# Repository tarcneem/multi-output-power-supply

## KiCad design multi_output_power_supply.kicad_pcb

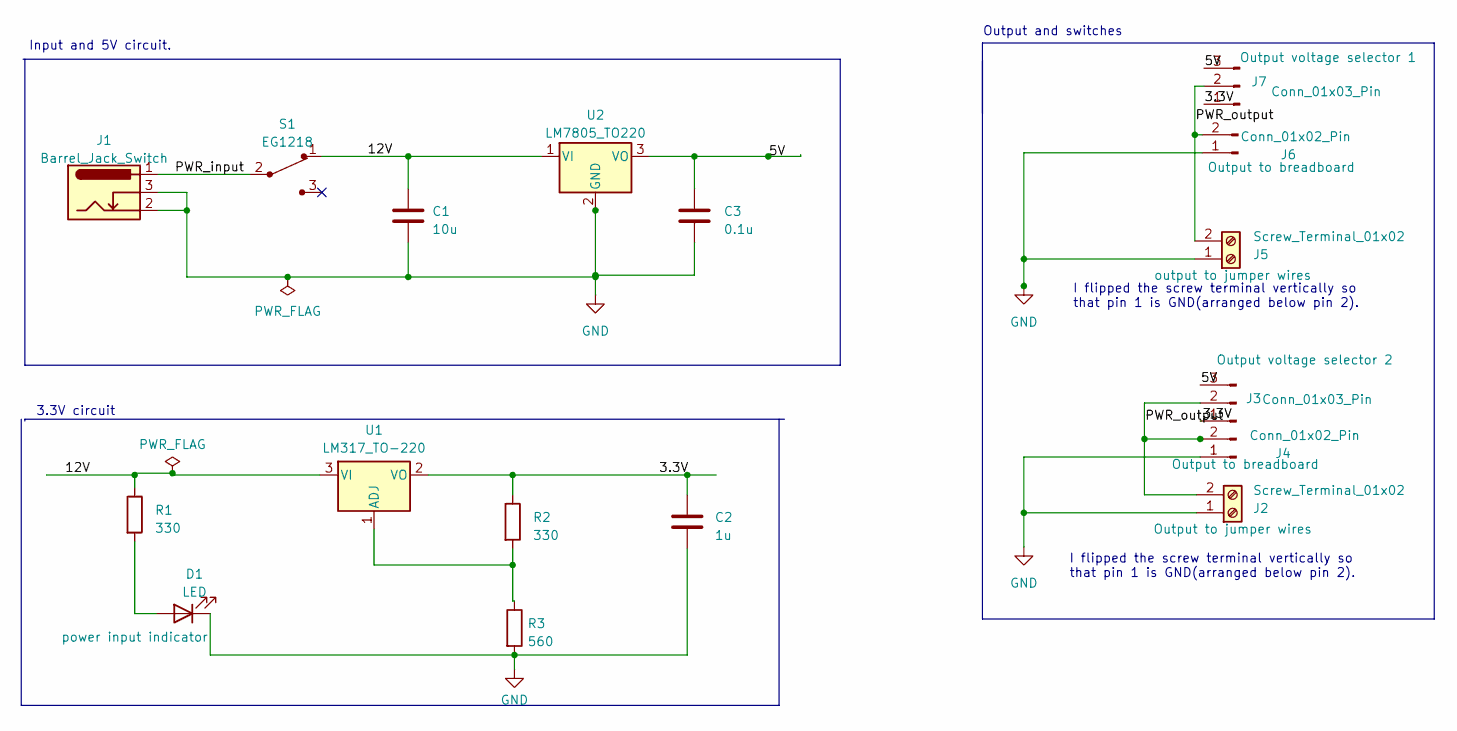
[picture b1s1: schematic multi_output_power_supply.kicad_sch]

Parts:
C1: 10u; C_Disc_D3.0mm_W1.6mm_P2.50mm
C2: 1u; C_Disc_D3.0mm_W1.6mm_P2.50mm
C3: 0.1u; C_Disc_D3.0mm_W1.6mm_P2.50mm
D1: LED; LED_D5.0mm
J1: Barrel_Jack_Switch; BarrelJack_Horizontal
J2, J5: Screw_Terminal_01x02; TerminalBlock_bornier-2_P5.08mm
J3, J7: Conn_01x03_Pin; PinHeader_1x03_P2.54mm_Vertical
J4, J6: Conn_01x02_Pin; PinHeader_1x02_P2.54mm_Vertical
R1, R2: 330; R_Axial_DIN0204_L3.6mm_D1.6mm_P7.62mm_Horizontal
R3: 560; R_Axial_DIN0204_L3.6mm_D1.6mm_P7.62mm_Horizontal
S1: EG1218; Switch_Slide_11.6x4mm_EG1218; MPN EG1218; Digi-Key_PN EG1903-ND
U1: LM317_TO-220; TO-220-3_Vertical
U2: LM7805_TO220; TO-220-3_Vertical

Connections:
/3.3V: C2.1, J3.1, J7.1, R2.1, U1.2 (VO)
/5V: C3.1, J3.3, J7.3, U2.3 (VO)
/12V: C1.1, R1.1, S1.1, U1.3 (VI), U2.1 (VI)
/PWR_input: J1.1, S1.2
/PWR_output: J2.2, J3.2, J4.2, J5.2, J6.2, J7.2
GND: C1.2, C2.2, C3.2, D1.1 (K), J1.2, J1.3, J2.1, J4.1, J5.1, J6.1, R3.2, U2.2 (GND)
unnamed: D1.2 (A), R1.2
unnamed: R2.2, R3.1, U1.1 (ADJ)

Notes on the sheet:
I flipped the screw terminal vertically so that pin 1 is GND(arranged below pin 2).
3.3V circuit
Output and switches
Input and 5V circuit.

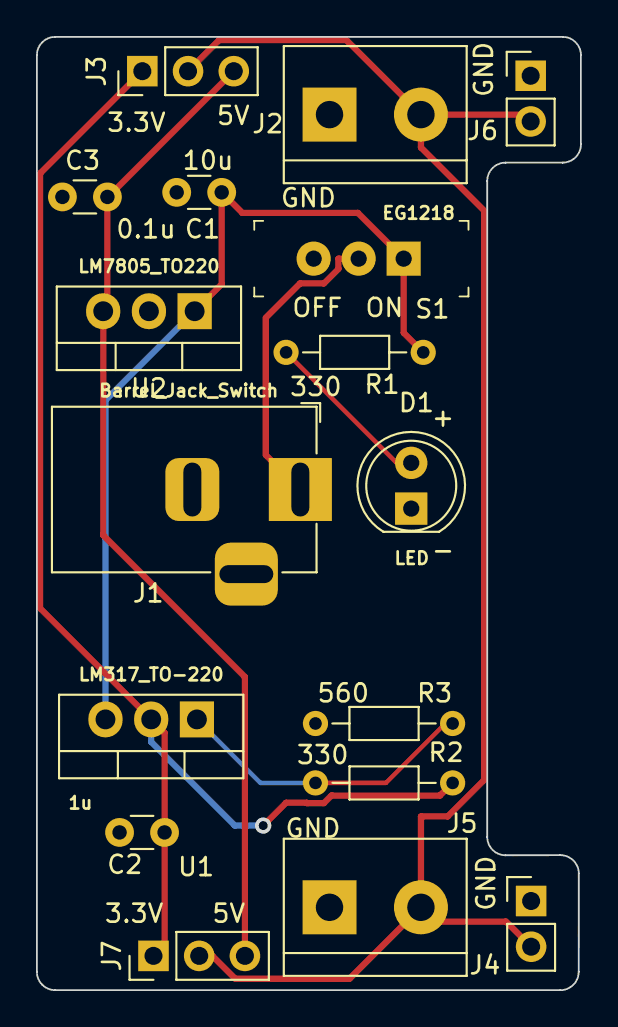
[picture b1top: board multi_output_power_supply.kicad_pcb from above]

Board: 2 copper layers, 30.2 x 53.0 mm, 17 parts (0 on the bottom side), 8 nets.

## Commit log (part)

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2026-04-19 Upload project files
